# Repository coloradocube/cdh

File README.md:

# cdh
Command and data handling board

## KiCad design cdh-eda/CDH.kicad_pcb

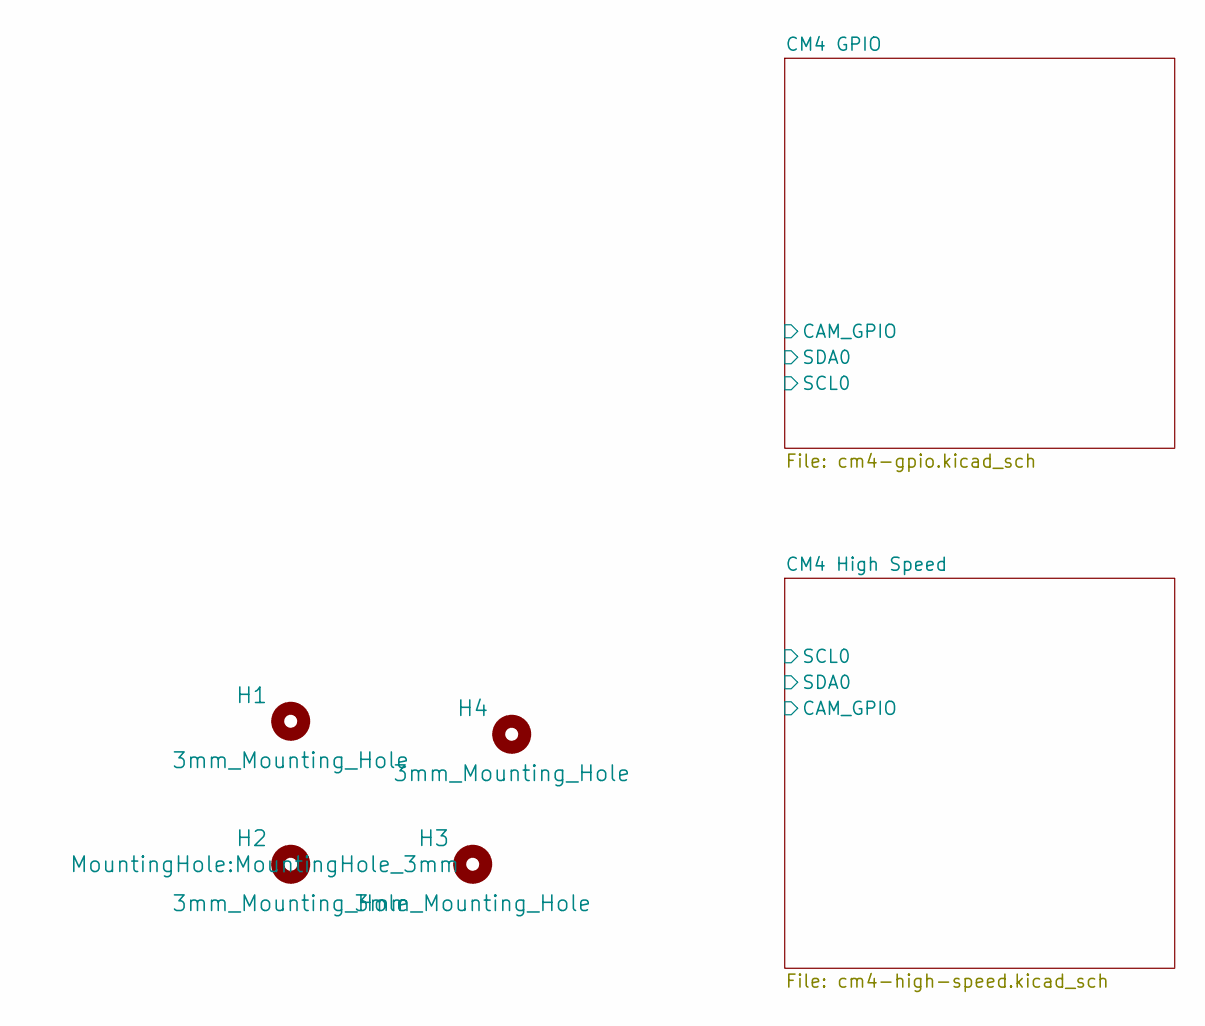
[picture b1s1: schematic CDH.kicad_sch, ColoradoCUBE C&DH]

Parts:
H1, H2, H3, H4: 3mm_Mounting_Hole; MountingHole_3mm

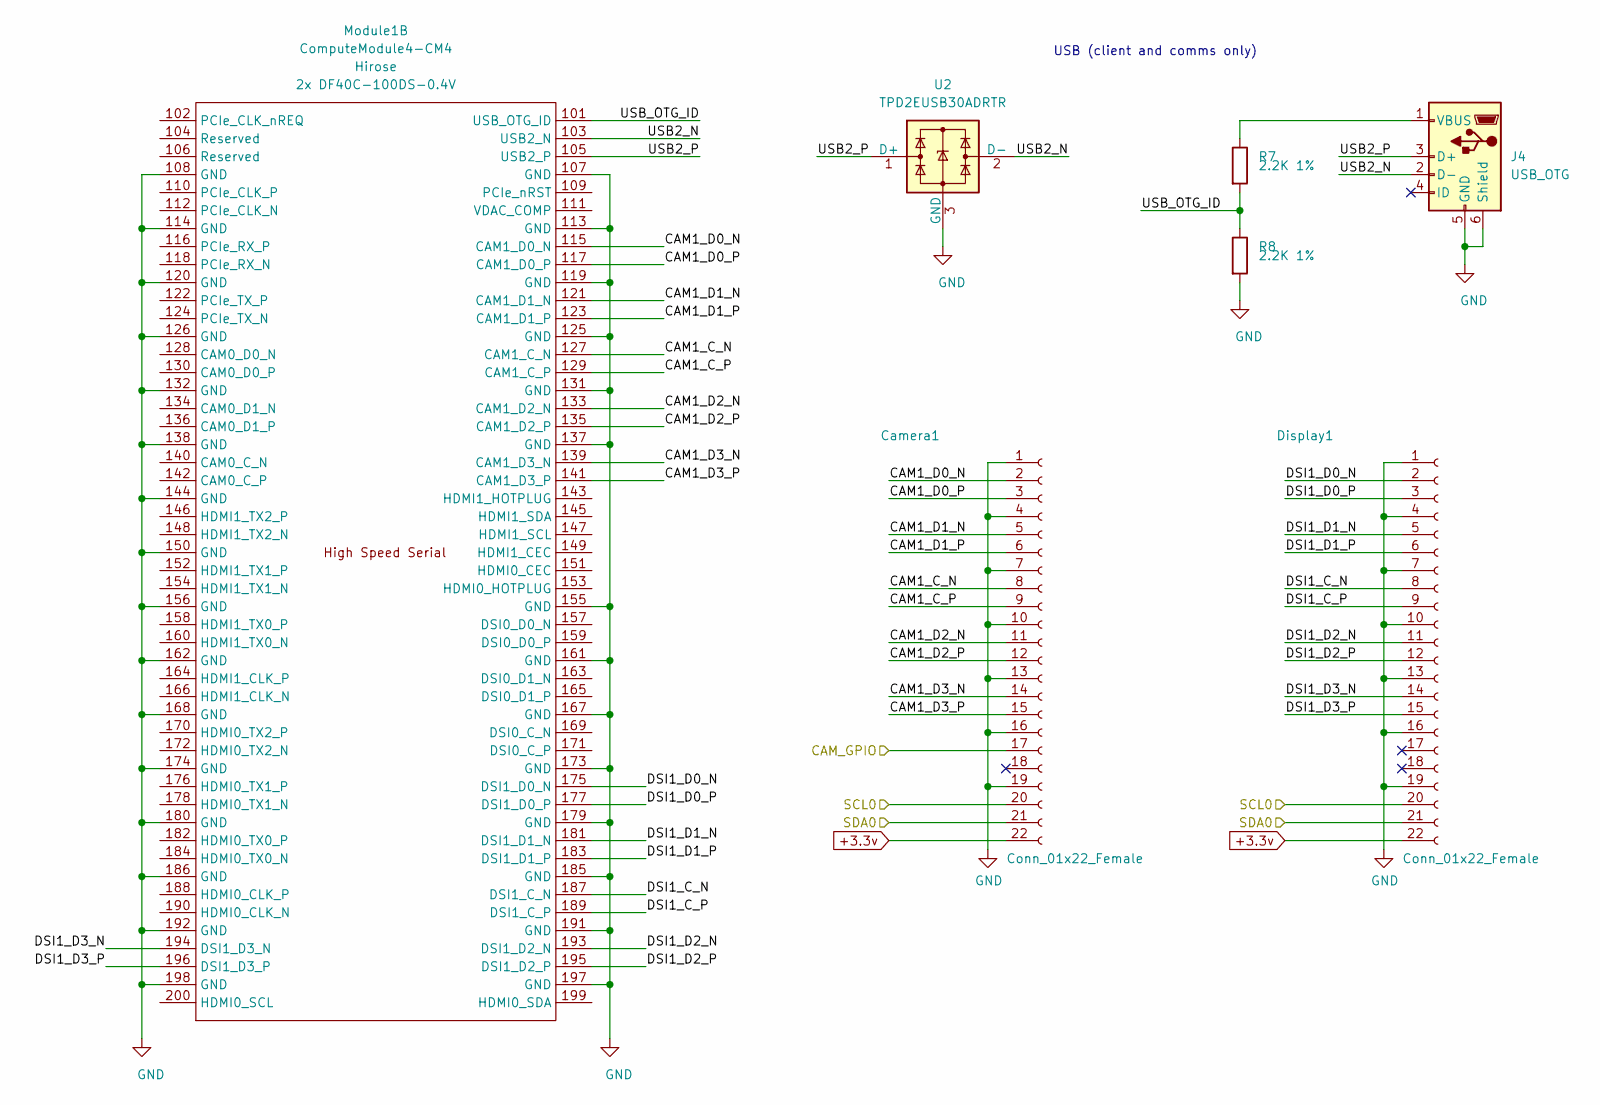
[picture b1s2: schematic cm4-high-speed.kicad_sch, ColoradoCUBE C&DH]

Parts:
Camera1: Conn_01x22_Female; Hirose_FH12-22S-0.5SH_1x22-1MP_P0.50mm_Horizontal; Part Description 22 Position FFC, FPC Connector Contacts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
Display1: Conn_01x22_Female; Hirose_FH12-22S-0.5SH_1x22-1MP_P0.50mm_Horizontal; Part Description 22 Position FFC, FPC Connector Contacts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
J4: USB_OTG; USB_Micro-B_EDAC_UCON00686; MPN 10103594-0001LF; Digi-Key_PN 609-4050-1-ND
Module1: ComputeModule4-CM4; Raspberry-Pi-4-Compute-Module; Digi-Key_PN 2x H11615CT-ND
R7, R8: 2.2K 1%; R_0603_1608Metric_Pad0.98x0.95mm_HandSolder; MPN RC0603FR-072K2L; Digi-Key_PN 311-2.20KHRCT-ND
U2: TPD2EUSB30ADRTR; Texas_DRT-3; MPN TPD2EUSB30ADRTR; Digi-Key_PN 296-25509-1-ND

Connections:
+3.3V: Camera1.22, Display1.22; also elsewhere on the board
+5V: Module1.77 (+5v_(Input)), Module1.79 (+5v_(Input)), Module1.81 (+5v_(Input)), Module1.83 (+5v_(Input)), Module1.85 (+5v_(Input)), Module1.87 (+5v_(Input)); also elsewhere on the board
/CM4 GPIO/GPIO2: Module1.58 (GPIO2); also elsewhere on the board
/CM4 GPIO/GPIO3: Module1.56 (GPIO3); also elsewhere on the board
/CM4 GPIO/GPIO8: Module1.39 (GPIO8); also elsewhere on the board
/CM4 GPIO/GPIO9: Module1.40 (GPIO9); also elsewhere on the board
/CM4 GPIO/GPIO10: Module1.44 (GPIO10); also elsewhere on the board
/CM4 GPIO/GPIO11: Module1.38 (GPIO11); also elsewhere on the board
/CM4 GPIO/GPIO14: Module1.55 (GPIO14); also elsewhere on the board
/CM4 GPIO/GPIO15: Module1.51 (GPIO15); also elsewhere on the board
/CM4 GPIO/GPIO18: Module1.49 (GPIO18); also elsewhere on the board
/CM4 GPIO/nLED_Activity: Module1.21 (PI_nLED_Activity); also elsewhere on the board
/CM4 GPIO/nPWR_LED: Module1.95 (nPI_LED_PWR); also elsewhere on the board
/CM4 GPIO/nRPIBOOT: Module1.93 (nRPIBOOT); also elsewhere on the board
/CM4 High Speed/CAM1_C_N: Camera1.8, Module1.127 (CAM1_C_N)
/CM4 High Speed/CAM1_C_P: Camera1.9, Module1.129 (CAM1_C_P)
/CM4 High Speed/CAM1_D0_N: Camera1.2, Module1.115 (CAM1_D0_N)
/CM4 High Speed/CAM1_D0_P: Camera1.3, Module1.117 (CAM1_D0_P)
/CM4 High Speed/CAM1_D1_N: Camera1.5, Module1.121 (CAM1_D1_N)
/CM4 High Speed/CAM1_D1_P: Camera1.6, Module1.123 (CAM1_D1_P)
/CM4 High Speed/CAM1_D2_N: Camera1.11, Module1.133 (CAM1_D2_N)
/CM4 High Speed/CAM1_D2_P: Camera1.12, Module1.135 (CAM1_D2_P)
/CM4 High Speed/CAM1_D3_N: Camera1.14, Module1.139 (CAM1_D3_N)
/CM4 High Speed/CAM1_D3_P: Camera1.15, Module1.141 (CAM1_D3_P)
/CM4 High Speed/CAM_GPIO: Camera1.17
/CM4 High Speed/DSI1_C_N: Display1.8, Module1.187 (DSI1_C_N)
/CM4 High Speed/DSI1_C_P: Display1.9, Module1.189 (DSI1_C_P)
/CM4 High Speed/DSI1_D0_N: Display1.2, Module1.175 (DSI1_D0_N)
/CM4 High Speed/DSI1_D0_P: Display1.3, Module1.177 (DSI1_D0_P)
/CM4 High Speed/DSI1_D1_N: Display1.5, Module1.181 (DSI1_D1_N)
/CM4 High Speed/DSI1_D1_P: Display1.6, Module1.183 (DSI1_D1_P)
/CM4 High Speed/DSI1_D2_N: Display1.11, Module1.193 (DSI1_D2_N)
/CM4 High Speed/DSI1_D2_P: Display1.12, Module1.195 (DSI1_D2_P)
/CM4 High Speed/DSI1_D3_N: Display1.14, Module1.194 (DSI1_D3_N)
/CM4 High Speed/DSI1_D3_P: Display1.15, Module1.196 (DSI1_D3_P)
/CM4 High Speed/SCL0: Camera1.20, Display1.20, Module1.80 (SCL0)
/CM4 High Speed/SDA0: Camera1.21, Display1.21, Module1.82 (SDA0)
/CM4 High Speed/USB2_N: J4.2 (D-), Module1.103 (USB2_N), U2.2 (D-)
/CM4 High Speed/USB2_P: J4.3 (D+), Module1.105 (USB2_P), U2.1 (D+)
/CM4 High Speed/USB_OTG_ID: Module1.101 (USB_OTG_ID), R7.2, R8.1
GND: Camera1.1, Camera1.4, Camera1.7, Camera1.10, Camera1.13, Camera1.16, Camera1.19, Display1.1, Display1.4, Display1.7, Display1.10, Display1.13, Display1.16, Display1.19, J4.5 (GND), J4.6 (Shield), Module1.1 (GND), Module1.2 (GND), Module1.7 (GND), Module1.8 (GND), Module1.13 (GND), Module1.14 (GND), Module1.22 (GND), Module1.23 (GND), Module1.32 (GND), Module1.33 (GND), Module1.42 (GND), Module1.43 (GND), Module1.52 (GND), Module1.53 (GND), Module1.59 (GND), Module1.60 (GND), Module1.65 (GND), Module1.66 (GND), Module1.71 (GND), Module1.74 (GND), Module1.98 (GND), Module1.107 (GND), Module1.108 (GND), Module1.113 (GND), Module1.114 (GND), Module1.119 (GND), Module1.120 (GND), Module1.125 (GND), Module1.126 (GND), Module1.131 (GND), Module1.132 (GND), Module1.137 (GND), Module1.138 (GND), Module1.144 (GND), Module1.150 (GND), Module1.155 (GND), Module1.156 (GND), Module1.161 (GND), Module1.162 (GND), Module1.167 (GND), Module1.168 (GND), Module1.173 (GND), Module1.174 (GND), Module1.179 (GND), Module1.180 (GND), Module1.185 (GND), Module1.186 (GND), Module1.191 (GND), Module1.192 (GND), Module1.197 (GND), Module1.198 (GND), R8.2, U2.3 (GND); also elsewhere on the board
unnamed: J4.1 (VBUS), R7.1

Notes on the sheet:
USB (client and comms only)

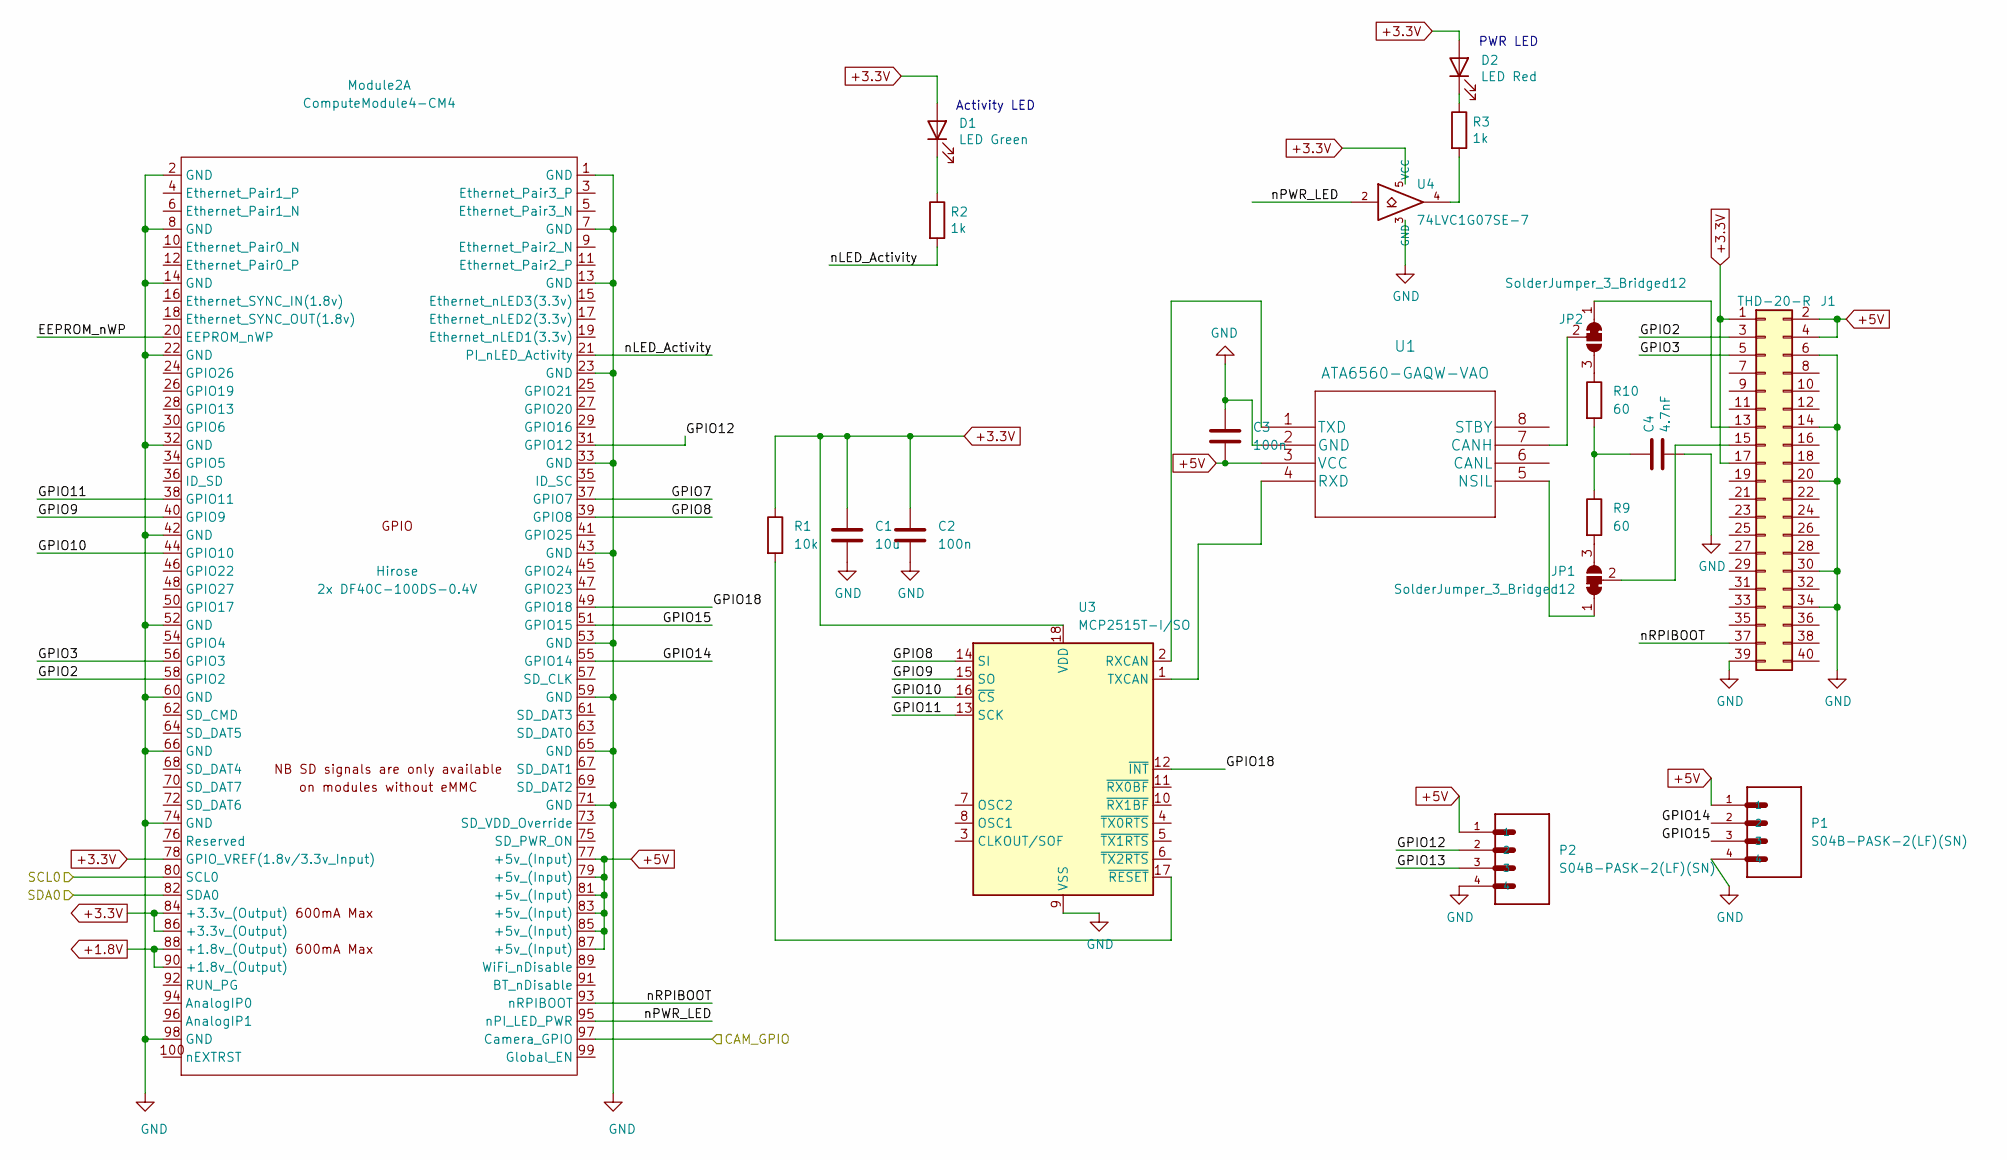
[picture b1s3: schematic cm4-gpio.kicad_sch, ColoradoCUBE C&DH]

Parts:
C1: 10u; C_0603_1608Metric
C2, C3: 100n; C_0603_1608Metric
C4: 4.7nF; C_0603_1608Metric; Voltage 25V; Mfr. # CL10B104KA8NNNC
D1: LED Green; LED_0603_1608Metric; Part Description Green 572nm LED Indication - Discrete 2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; Digi-Key_PN 160-1478-1-ND
D2: LED Red; LED_0603_1608Metric; Part Description Red 620nm LED Indication - Discrete 2.2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; Digi-Key_PN 160-1479-1-ND
J1: THD-20-R; PinHeader_2x20_P2.54mm_Vertical; Part Description PinHeader_2x20_P2.54mm_Vertical
JP1, JP2: SolderJumper_3_Bridged12; SolderJumper-3_P1.3mm_Bridged2Bar12_RoundedPad1.0x1.5mm
Module2: ComputeModule4-CM4; Raspberry-Pi-4-Compute-Module; MPN 2x DF40C-100DS-0.4V; Digi-Key_PN 2x H11615CT-ND
P1, P2: S04B-PASK-2(LF)(SN); JST_S04B-PASK-2(LF)(SN)
R1: 10k; R_0603_1608Metric
R2, R3: 1k; R_0603_1608Metric_Pad0.98x0.95mm_HandSolder; MPN RC0603FR-071KL; Digi-Key_PN 311-1.00KHRCT-ND
R9, R10: 60; R_0603_1608Metric
U1: ATA6560-GAQW-VAO; SOIC-8-1EP_3.9x4.9mm_P1.27mm_EP2.29x3mm
U3: MCP2515T-I/SO; SOIC-18W_7.5x11.6mm_P1.27mm
U4: 74LVC1G07SE-7; SOT-353_SC-70-5; Part Description Buffer, Non-Inverting 1 Element 1 Bit p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; Digi-Key_PN 74LVC1G07SE-7DICT-ND

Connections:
+3.3V: C1.1, C2.1, D1.2 (A), D2.2 (A), J1.1, J1.17, Module2.78 (GPIO_VREF(1.8v/3.3v_Input)), Module2.84 (+3.3v_(Output)), Module2.86 (+3.3v_(Output)), R1.1, U3.18 (VDD), U4.5 (VCC); also elsewhere on the board
+5V: C3.1, J1.2, J1.4, Module2.77 (+5v_(Input)), Module2.79 (+5v_(Input)), Module2.81 (+5v_(Input)), Module2.83 (+5v_(Input)), Module2.85 (+5v_(Input)), Module2.87 (+5v_(Input)), P1.1, P2.1, U1.3 (VCC); also elsewhere on the board
/CM4 GPIO/GPIO2: J1.3, Module2.58 (GPIO2); also elsewhere on the board
/CM4 GPIO/GPIO3: J1.5, Module2.56 (GPIO3); also elsewhere on the board
/CM4 GPIO/GPIO8: Module2.39 (GPIO8), U3.14 (SI); also elsewhere on the board
/CM4 GPIO/GPIO9: Module2.40 (GPIO9), U3.15 (SO); also elsewhere on the board
/CM4 GPIO/GPIO10: Module2.44 (GPIO10), U3.16 (~CS); also elsewhere on the board
/CM4 GPIO/GPIO11: Module2.38 (GPIO11), U3.13 (SCK); also elsewhere on the board
/CM4 GPIO/GPIO12: Module2.31 (GPIO12), P2.2
/CM4 GPIO/GPIO13: P2.3
/CM4 GPIO/GPIO14: Module2.55 (GPIO14), P1.2; also elsewhere on the board
/CM4 GPIO/GPIO15: Module2.51 (GPIO15), P1.3; also elsewhere on the board
/CM4 GPIO/GPIO18: Module2.49 (GPIO18), U3.12 (~INT); also elsewhere on the board
/CM4 GPIO/nLED_Activity: Module2.21 (PI_nLED_Activity), R2.2; also elsewhere on the board
/CM4 GPIO/nPWR_LED: Module2.95 (nPI_LED_PWR), U4.2; also elsewhere on the board
/CM4 GPIO/nRPIBOOT: J1.37, Module2.93 (nRPIBOOT); also elsewhere on the board
GND: C1.2, C2.2, C3.2, C4.2, J1.6, J1.14, J1.20, J1.30, J1.34, J1.39, Module2.1 (GND), Module2.2 (GND), Module2.7 (GND), Module2.8 (GND), Module2.13 (GND), Module2.14 (GND), Module2.22 (GND), Module2.23 (GND), Module2.32 (GND), Module2.33 (GND), Module2.42 (GND), Module2.43 (GND), Module2.52 (GND), Module2.53 (GND), Module2.59 (GND), Module2.60 (GND), Module2.65 (GND), Module2.66 (GND), Module2.71 (GND), Module2.74 (GND), Module2.98 (GND), P1.4, P2.4, U1.2 (GND), U3.9 (VSS), U4.3 (GND); also elsewhere on the board
unnamed: C4.1, R9.1, R10.2
unnamed: D1.1 (K), R2.1
unnamed: D2.1 (K), R3.1
unnamed: J1.13, JP2.1 (A)
unnamed: J1.15, JP1.2 (C)
unnamed: Module2.88 (+1.8v_(Output)), Module2.90 (+1.8v_(Output))
unnamed: R1.2, U3.17 (~RESET)
unnamed: R3.2, U4.4
unnamed: JP1.3 (B), R9.2
unnamed: JP2.3 (B), R10.1
unnamed: U1.1 (TXD), U3.2 (RXCAN)
unnamed: U1.4 (RXD), U3.1 (TXCAN)
unnamed: JP1.1 (A), U1.5 (NSIL)
unnamed: JP2.2 (C), U1.7 (CANH)

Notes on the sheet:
PWR LED
Activity LED

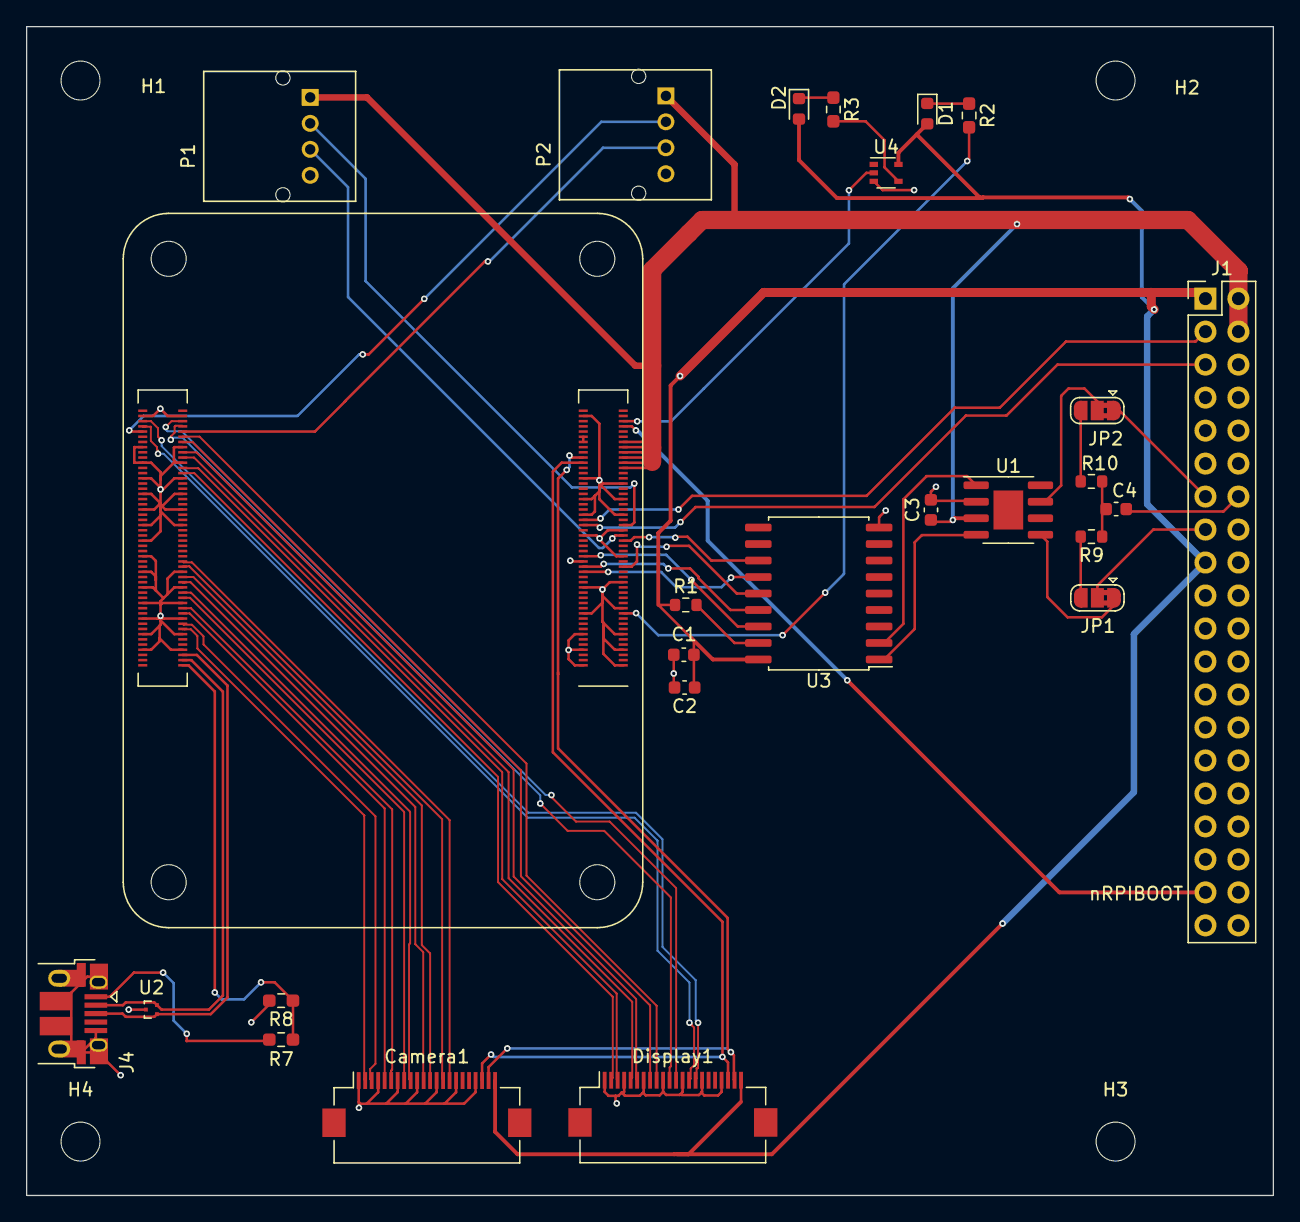
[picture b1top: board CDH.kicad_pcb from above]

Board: 2 copper layers, 96.0 x 90.0 mm, 30 parts (0 on the bottom side), 54 nets.

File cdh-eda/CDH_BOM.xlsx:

Id | Designator | Package | Quantity | Part Number | Supplier and ref | JLC avaliability | Links | _2
1 | R7,R8 | R_0603_1608Metric_Pad0.98x0.95mm_HandSolder | 2 | 2.2K 1% |  | yes
2 | Camera1,Display1 | Hirose_FH12-22S-0.5SH_1x22-1MP_P0.50mm_Horizontal | 2 | 798-FH12-22S-0.5SH55 | digikey | no | https://www.digikey.com/en/products/detail/hirose-electric-c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
3 | R2,R3 | R_0603_1608Metric_Pad0.98x0.95mm_HandSolder | 2 | 1k |  | yes
4 | H4,H2,H1,H3 | MountingHole_3mm | 4 | 3mm_Mounting_Hole
5 | JP1,JP2 | SolderJumper-3_P1.3mm_Bridged2Bar12_RoundedPad1.0x1.5mm | 2 | SolderJumper_3_Bridged12
6 | C4 | C_0603_1608Metric | 1 | 4.7nF |  | yes
7 | D1 | LED_0603_1608Metric | 1 | LED Green |  | yes
8 | P1,P2 | JST_S04B-PASK-2(LF)(SN) | 2 | S04B-PASK-2(LF)(SN) | digikey | no | https://www.digikey.com/en/products/detail/jst-sales-america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
9 | U1 | SOIC-8-1EP_3.9x4.9mm_P1.27mm_EP2.29x3mm | 1 | ATA6560-GAQW-VAO | on hand | no
10 | U4 | SOT-353_SC-70-5 | 1 | 74LVC1G07SE-7 |  | yes
11 | D2 | LED_0603_1608Metric | 1 | LED Red |  | yes
12 | C2,C3 | C_0603_1608Metric | 2 | 100n |  | yes
13 | U3 | SOIC-18W_7.5x11.6mm_P1.27mm | 1 | MCP2515T-I/SO |  | yes
14 | J4 | USB_Micro-B_EDAC_UCON00686 | 1 | 1050170001 |  | yes
15 | C1 | C_0603_1608Metric | 1 | 10u |  | yes
16 | U2 | Texas_DRT-3 | 1 | TPD2EUSB30ADRTR |  | yes
17 | R10,R9 | R_0603_1608Metric | 2 | 60 |  | yes
18 | Module1 | Raspberry-Pi-4-Compute-Module | 2 | DF40C-100DS-0.4V | heilind | no | https://www.heilind.com/hirdf40c-100ds-0-4v-51-p.html?&utm_s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
19 | R1 | R_0603_1608Metric | 1 | 10k |  | yes
20 | J1 | PinHeader_2x20_P2.54mm_Vertical | 1 | SSQ-120-03-F-D | digikey | no | https://www.digikey.com/en/products/detail/samtec-inc/SSQ-12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

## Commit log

2022-04-21 first separate cdh commit
2022-04-24 V.2 updates
    1. Add jumper CAN resistors
    2. Add camera connector
    3. Add display connector
    5. Updated CAN transceiver protective circuitry
    6. Add MCP2515 interrupt GPIO pin 18
2022-04-24 v.2 updates
    created separate BOMS for JCLPCB and In house purchases
2022-04-24 v.2
    moved boms into eda folder
2022-05-03 bom directory
2022-05-04 ignore excel and zip
